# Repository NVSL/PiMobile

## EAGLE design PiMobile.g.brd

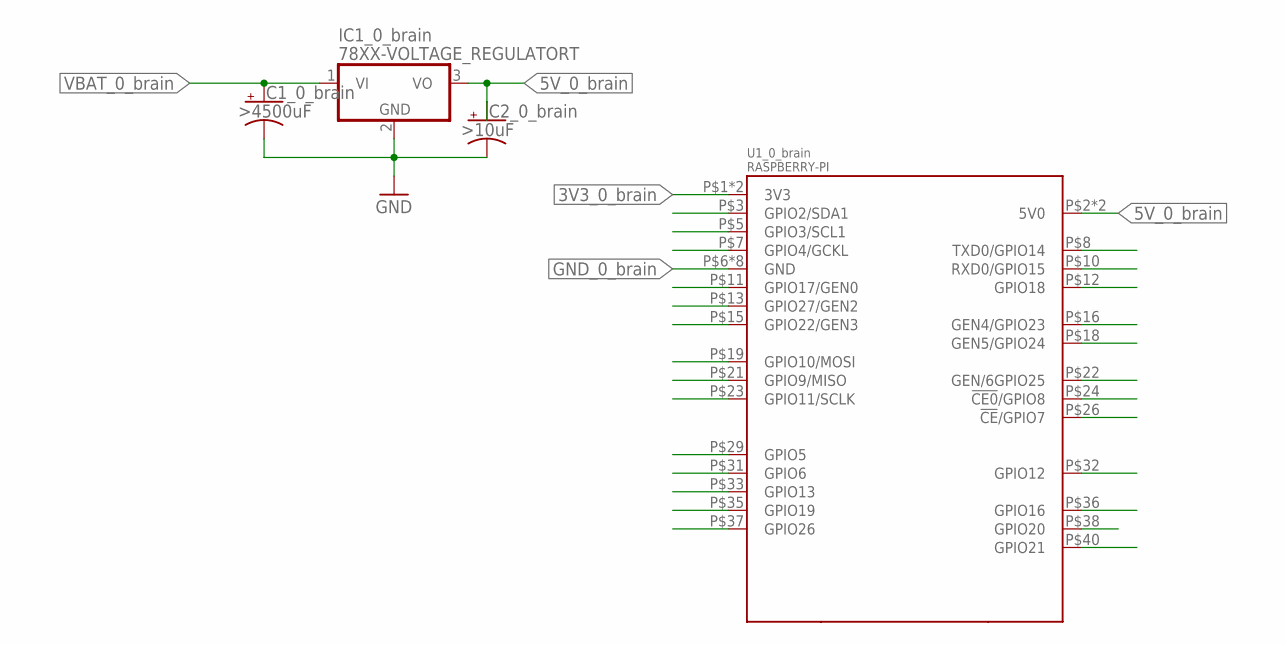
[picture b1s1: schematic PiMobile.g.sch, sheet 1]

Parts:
IC1_0_brain: 78XX-VOLTAGE_REGULATORT; TO220H
U1_0_brain: RASPBERRY-PI; RPI-ZERO-EDGE-RIGHT-ANGLE

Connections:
3V3_0_brain: U1_0_brain.P$1 (3V3), U1_0_brain.P$17 (3V3)
5V_0_brain: IC1_0_brain.3 (VO), U1_0_brain.P$2 (5V0), U1_0_brain.P$4 (5V0); also elsewhere on the board
!CE0!/GPIO8_0_brain: U1_0_brain.P$24 (!CE0!/GPIO8); also elsewhere on the board
!CE!/GPIO7_0_brain: U1_0_brain.P$26 (!CE!/GPIO7); also elsewhere on the board
GEN4/GPIO23_0_brain: U1_0_brain.P$16 (GEN4/GPIO23)
GEN5/GPIO24_0_brain: U1_0_brain.P$18 (GEN5/GPIO24)
GEN/6GPIO25_0_brain: U1_0_brain.P$22 (GEN/6GPIO25)
GND_0_brain: IC1_0_brain.2 (GND), U1_0_brain.P$6 (GND), U1_0_brain.P$9 (GND), U1_0_brain.P$14 (GND), U1_0_brain.P$20 (GND), U1_0_brain.P$25 (GND), U1_0_brain.P$30 (GND), U1_0_brain.P$34 (GND), U1_0_brain.P$39 (GND); also elsewhere on the board
GPIO2/SDA1_0_brain: U1_0_brain.P$3 (GPIO2/SDA1); also elsewhere on the board
GPIO3/SCL1_0_brain: U1_0_brain.P$5 (GPIO3/SCL1); also elsewhere on the board
GPIO4/GCKL_0_brain: U1_0_brain.P$7 (GPIO4/GCKL); also elsewhere on the board
GPIO5_0_brain: U1_0_brain.P$29 (GPIO5); also elsewhere on the board
GPIO6_0_brain: U1_0_brain.P$31 (GPIO6); also elsewhere on the board
GPIO9/MISO_0_brain: U1_0_brain.P$21 (GPIO9/MISO); also elsewhere on the board
GPIO10/MOSI_0_brain: U1_0_brain.P$19 (GPIO10/MOSI); also elsewhere on the board
GPIO11/SCLK_0_brain: U1_0_brain.P$23 (GPIO11/SCLK); also elsewhere on the board
GPIO12_0_brain: U1_0_brain.P$32 (GPIO12); also elsewhere on the board
GPIO13_0_brain: U1_0_brain.P$33 (GPIO13); also elsewhere on the board
GPIO16_0_brain: U1_0_brain.P$36 (GPIO16); also elsewhere on the board
GPIO17/GEN0_0_brain: U1_0_brain.P$11 (GPIO17/GEN0); also elsewhere on the board
GPIO18_0_brain: U1_0_brain.P$12 (GPIO18); also elsewhere on the board
GPIO19_0_brain: U1_0_brain.P$35 (GPIO19); also elsewhere on the board
GPIO20_0_brain: U1_0_brain.P$38 (GPIO20); also elsewhere on the board
GPIO21_0_brain: U1_0_brain.P$40 (GPIO21)
GPIO22/GEN3_0_brain: U1_0_brain.P$15 (GPIO22/GEN3)
GPIO26_0_brain: U1_0_brain.P$37 (GPIO26)
GPIO27/GEN2_0_brain: U1_0_brain.P$13 (GPIO27/GEN2)
RXD0/GPIO15_0_brain: U1_0_brain.P$10 (RXD0/GPIO15); also elsewhere on the board
TXD0/GPIO14_0_brain: U1_0_brain.P$8 (TXD0/GPIO14); also elsewhere on the board
VBAT_0_brain: IC1_0_brain.1 (VI)

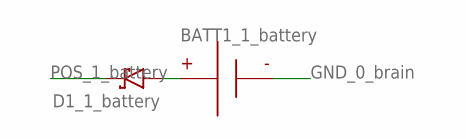
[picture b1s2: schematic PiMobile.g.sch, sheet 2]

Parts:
BATT1_1_battery: BATTERY-9V-VERTICAL; BATTERY_9V_KEYSTONE_968

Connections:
GND_0_brain: BATT1_1_battery.N; also elsewhere on the board

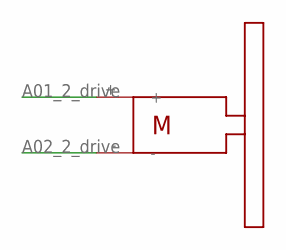
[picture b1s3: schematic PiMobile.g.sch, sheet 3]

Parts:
R_2_drive: SOLARBOTICS_GM2; SOLARBOTICS_G2

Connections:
A01_2_drive: R_2_drive.+; also elsewhere on the board
A02_2_drive: R_2_drive.-; also elsewhere on the board

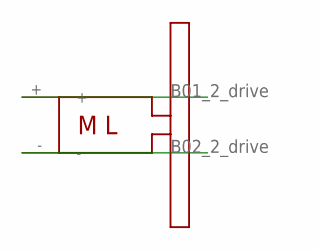
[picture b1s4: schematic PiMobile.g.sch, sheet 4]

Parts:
L_2_drive: SOLARBOTICS_GM2_LEFT; SOLARBOTICS_G2_LEFT

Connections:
B01_2_drive: L_2_drive.+; also elsewhere on the board
B02_2_drive: L_2_drive.-; also elsewhere on the board

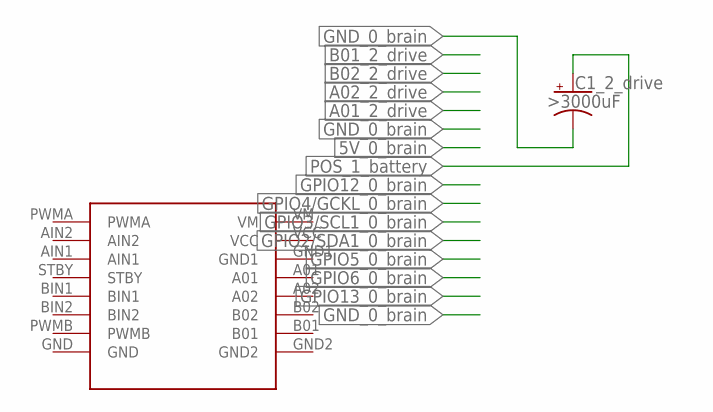
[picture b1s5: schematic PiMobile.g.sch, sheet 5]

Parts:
DRVR_2_drive: SPARKFUN_DUAL_MOTOR_DRIVER-BOB; SPARKFUN_DUAL_MOTOR_DRIVER

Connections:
5V_0_brain: DRVR_2_drive.VCC; also elsewhere on the board
A01_2_drive: DRVR_2_drive.A01; also elsewhere on the board
A02_2_drive: DRVR_2_drive.A02; also elsewhere on the board
B01_2_drive: DRVR_2_drive.B01; also elsewhere on the board
B02_2_drive: DRVR_2_drive.B02; also elsewhere on the board
GND_0_brain: DRVR_2_drive.GND, DRVR_2_drive.GND1, DRVR_2_drive.GND2; also elsewhere on the board
GPIO2/SDA1_0_brain: DRVR_2_drive.STBY; also elsewhere on the board
GPIO3/SCL1_0_brain: DRVR_2_drive.AIN1; also elsewhere on the board
GPIO4/GCKL_0_brain: DRVR_2_drive.AIN2; also elsewhere on the board
GPIO5_0_brain: DRVR_2_drive.BIN1; also elsewhere on the board
GPIO6_0_brain: DRVR_2_drive.BIN2; also elsewhere on the board
GPIO12_0_brain: DRVR_2_drive.PWMA; also elsewhere on the board
GPIO13_0_brain: DRVR_2_drive.PWMB; also elsewhere on the board
POS_1_battery: DRVR_2_drive.VM

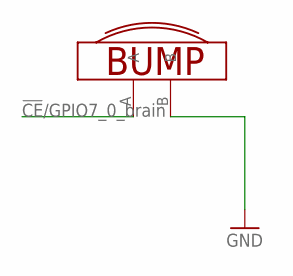
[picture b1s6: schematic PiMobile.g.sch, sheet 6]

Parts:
U$2_3_bump: BUMP_SWITCH-MEDIUM-LEFT; BUMP_SWITCH_OMRON_D2FLA

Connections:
!CE!/GPIO7_0_brain: U$2_3_bump.A; also elsewhere on the board
GND_0_brain: U$2_3_bump.B; also elsewhere on the board

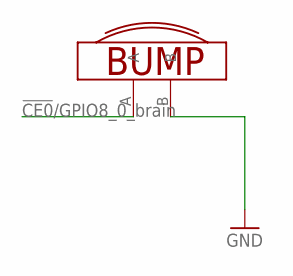
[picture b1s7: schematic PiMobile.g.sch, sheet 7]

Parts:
U$2_4_bump_2: BUMP_SWITCH-MEDIUM-RIGHT; BUMP_SWITCH_OMRON_D2FLA1

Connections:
!CE0!/GPIO8_0_brain: U$2_4_bump_2.A; also elsewhere on the board
GND_0_brain: U$2_4_bump_2.B; also elsewhere on the board

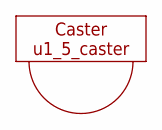
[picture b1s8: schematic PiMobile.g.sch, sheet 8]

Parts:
u1_5_caster: CASTERADAFRUIT-3/4IN; ADAFRUIT-3/4IN-CASTER

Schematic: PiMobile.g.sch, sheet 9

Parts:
LED1_6_led: LED5MM

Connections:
GPIO9/MISO_0_brain: LED1_6_led.A; also elsewhere on the board

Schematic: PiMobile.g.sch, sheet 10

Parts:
LED1_7_led_2: LED5MM

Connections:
GPIO10/MOSI_0_brain: LED1_7_led_2.A; also elsewhere on the board

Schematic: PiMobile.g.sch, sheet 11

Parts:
U$2_8_bump_3: BUMP_SWITCH-MEDIUM-LEFT; BUMP_SWITCH_OMRON_D2FLA

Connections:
GND_0_brain: U$2_8_bump_3.B; also elsewhere on the board
GPIO11/SCLK_0_brain: U$2_8_bump_3.A; also elsewhere on the board

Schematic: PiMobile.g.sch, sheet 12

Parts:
U$2_9_bump_4: BUMP_SWITCH-MEDIUM-RIGHT; BUMP_SWITCH_OMRON_D2FLA1

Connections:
GND_0_brain: U$2_9_bump_4.B; also elsewhere on the board
TXD0/GPIO14_0_brain: U$2_9_bump_4.A; also elsewhere on the board

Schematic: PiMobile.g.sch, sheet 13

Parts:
u1_10_penholder: PENHOLDER

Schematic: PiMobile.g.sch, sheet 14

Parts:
B1_11_button: BUTTON-TACTILE-ROUND; BUTTON-TACTILE-ROUND-ADAFRUIT1009

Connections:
GND_0_brain: B1_11_button.S; also elsewhere on the board
RXD0/GPIO15_0_brain: B1_11_button.P; also elsewhere on the board

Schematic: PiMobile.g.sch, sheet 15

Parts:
B1_12_button_2: BUTTON-TACTILE-ROUND; BUTTON-TACTILE-ROUND-ADAFRUIT1009

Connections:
GND_0_brain: B1_12_button_2.S; also elsewhere on the board
GPIO16_0_brain: B1_12_button_2.P; also elsewhere on the board

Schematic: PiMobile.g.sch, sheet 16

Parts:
LED1_13_led_3: LED5MM

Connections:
GPIO17/GEN0_0_brain: LED1_13_led_3.A; also elsewhere on the board

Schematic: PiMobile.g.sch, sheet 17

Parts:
LED1_14_led_4: LED5MM

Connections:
GPIO18_0_brain: LED1_14_led_4.A; also elsewhere on the board

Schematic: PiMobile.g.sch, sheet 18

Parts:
LED1_15_led_5: LED5MM

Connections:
GPIO19_0_brain: LED1_15_led_5.A; also elsewhere on the board

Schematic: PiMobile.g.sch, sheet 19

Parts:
LED1_16_led_6: LED5MM

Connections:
GPIO20_0_brain: LED1_16_led_6.A; also elsewhere on the board

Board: 2 copper layers, 20 parts (0 on the bottom side), 26 nets, no tracks yet.

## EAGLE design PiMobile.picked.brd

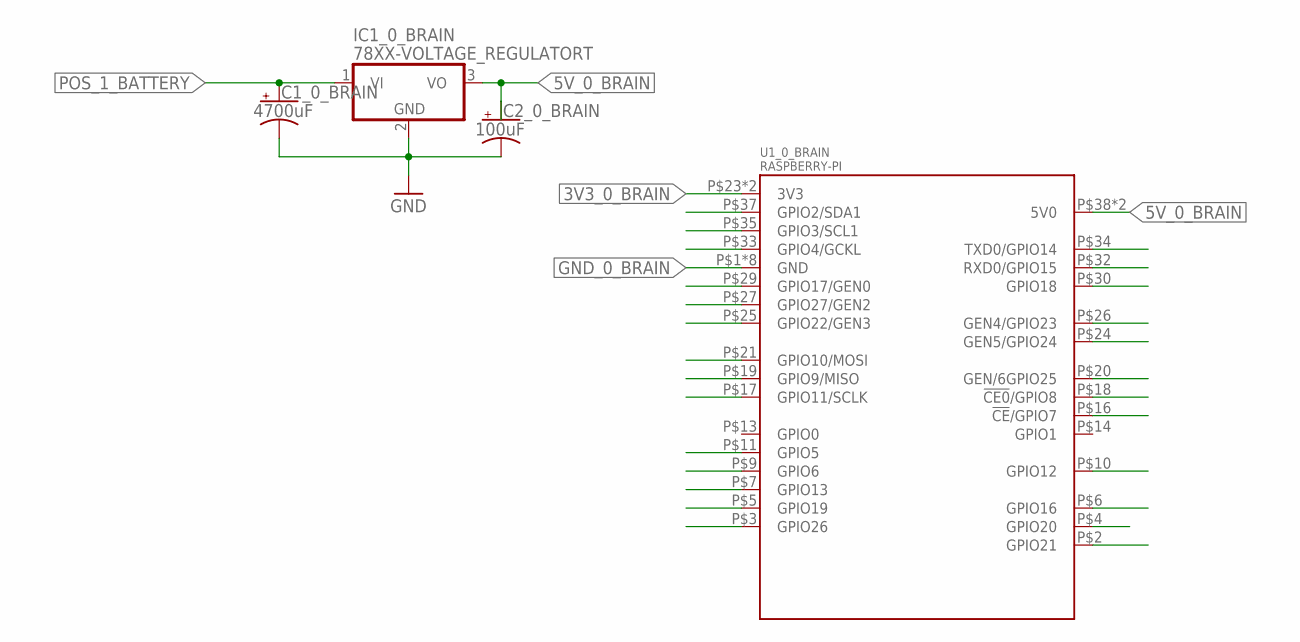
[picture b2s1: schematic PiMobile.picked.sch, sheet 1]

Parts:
C1_0_BRAIN: 4700uF; CAPPRD750W80D1600H2200P; MPN ECA-1EM472
C2_0_BRAIN: 100uF; CAPPRD250W80D630H1220P; MPN ECA-1EM101
IC1_0_BRAIN: 78XX-VOLTAGE_REGULATORT; TO220H
U1_0_BRAIN: RASPBERRY-PI; RPI-ZERO-EDGE-RIGHT-ANGLE

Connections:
3V3_0_BRAIN: U1_0_BRAIN.P$23 (3V3), U1_0_BRAIN.P$39 (3V3); also elsewhere on the board
5V_0_BRAIN: C2_0_BRAIN.1 (+), IC1_0_BRAIN.3 (VO), U1_0_BRAIN.P$38 (5V0), U1_0_BRAIN.P$40 (5V0)
!CE0!/GPIO8_0_BRAIN: U1_0_BRAIN.P$18 (!CE0!/GPIO8); also elsewhere on the board
!CE!/GPIO7_0_BRAIN: U1_0_BRAIN.P$16 (!CE!/GPIO7); also elsewhere on the board
GEN4/GPIO23_0_BRAIN: U1_0_BRAIN.P$26 (GEN4/GPIO23)
GEN5/GPIO24_0_BRAIN: U1_0_BRAIN.P$24 (GEN5/GPIO24)
GEN/6GPIO25_0_BRAIN: U1_0_BRAIN.P$20 (GEN/6GPIO25)
GND_0_BRAIN: C1_0_BRAIN.2 (-), C2_0_BRAIN.2 (-), IC1_0_BRAIN.2 (GND), U1_0_BRAIN.P$1 (GND), U1_0_BRAIN.P$8 (GND), U1_0_BRAIN.P$12 (GND), U1_0_BRAIN.P$15 (GND), U1_0_BRAIN.P$22 (GND), U1_0_BRAIN.P$28 (GND), U1_0_BRAIN.P$31 (GND), U1_0_BRAIN.P$36 (GND); also elsewhere on the board
GPIO2/SDA1_0_BRAIN: U1_0_BRAIN.P$37 (GPIO2/SDA1); also elsewhere on the board
GPIO3/SCL1_0_BRAIN: U1_0_BRAIN.P$35 (GPIO3/SCL1); also elsewhere on the board
GPIO4/GCKL_0_BRAIN: U1_0_BRAIN.P$33 (GPIO4/GCKL); also elsewhere on the board
GPIO5_0_BRAIN: U1_0_BRAIN.P$11 (GPIO5); also elsewhere on the board
GPIO6_0_BRAIN: U1_0_BRAIN.P$9 (GPIO6); also elsewhere on the board
GPIO9/MISO_0_BRAIN: U1_0_BRAIN.P$19 (GPIO9/MISO); also elsewhere on the board
GPIO10/MOSI_0_BRAIN: U1_0_BRAIN.P$21 (GPIO10/MOSI); also elsewhere on the board
GPIO11/SCLK_0_BRAIN: U1_0_BRAIN.P$17 (GPIO11/SCLK); also elsewhere on the board
GPIO12_0_BRAIN: U1_0_BRAIN.P$10 (GPIO12); also elsewhere on the board
GPIO13_0_BRAIN: U1_0_BRAIN.P$7 (GPIO13); also elsewhere on the board
GPIO16_0_BRAIN: U1_0_BRAIN.P$6 (GPIO16); also elsewhere on the board
GPIO17/GEN0_0_BRAIN: U1_0_BRAIN.P$29 (GPIO17/GEN0); also elsewhere on the board
GPIO18_0_BRAIN: U1_0_BRAIN.P$30 (GPIO18); also elsewhere on the board
GPIO19_0_BRAIN: U1_0_BRAIN.P$5 (GPIO19); also elsewhere on the board
GPIO20_0_BRAIN: U1_0_BRAIN.P$4 (GPIO20); also elsewhere on the board
GPIO21_0_BRAIN: U1_0_BRAIN.P$2 (GPIO21)
GPIO22/GEN3_0_BRAIN: U1_0_BRAIN.P$25 (GPIO22/GEN3)
GPIO26_0_BRAIN: U1_0_BRAIN.P$3 (GPIO26)
GPIO27/GEN2_0_BRAIN: U1_0_BRAIN.P$27 (GPIO27/GEN2)
POS_1_BATTERY: C1_0_BRAIN.1 (+), IC1_0_BRAIN.1 (VI); also elsewhere on the board
RXD0/GPIO15_0_BRAIN: U1_0_BRAIN.P$32 (RXD0/GPIO15); also elsewhere on the board
TXD0/GPIO14_0_BRAIN: U1_0_BRAIN.P$34 (TXD0/GPIO14); also elsewhere on the board

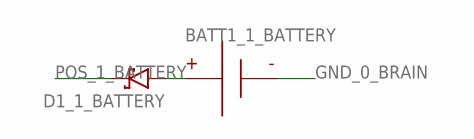
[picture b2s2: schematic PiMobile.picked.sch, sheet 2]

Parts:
BATT1_1_BATTERY: BATTERY-9V-VERTICAL; BATTERY_9V_KEYSTONE_968
D1_1_BATTERY: RESOLVED-DIODE-SCHOTTKY_TH-DO-41-AND-DO-204AL; DIOAD1125W78L520D270_HS; MPN 1N5817

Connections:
GND_0_BRAIN: BATT1_1_BATTERY.N; also elsewhere on the board
unnamed: BATT1_1_BATTERY.P, D1_1_BATTERY.A
POS_1_BATTERY: D1_1_BATTERY.C; also elsewhere on the board

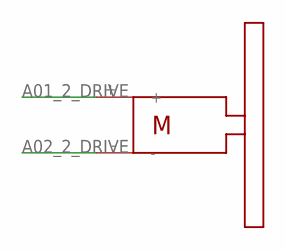
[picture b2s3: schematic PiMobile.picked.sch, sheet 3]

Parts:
R_2_DRIVE: SOLARBOTICS_GM2; SOLARBOTICS_G2

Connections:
A01_2_DRIVE: R_2_DRIVE.+; also elsewhere on the board
A02_2_DRIVE: R_2_DRIVE.-; also elsewhere on the board

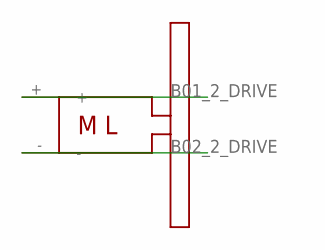
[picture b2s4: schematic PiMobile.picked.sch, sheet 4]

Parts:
L_2_DRIVE: SOLARBOTICS_GM2_LEFT; SOLARBOTICS_G2_LEFT

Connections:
B01_2_DRIVE: L_2_DRIVE.+; also elsewhere on the board
B02_2_DRIVE: L_2_DRIVE.-; also elsewhere on the board

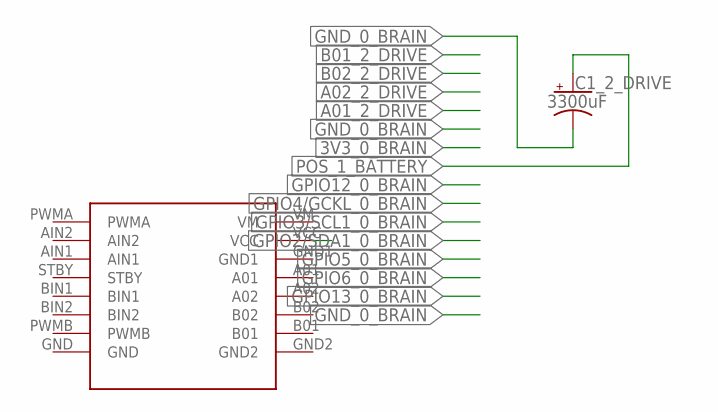
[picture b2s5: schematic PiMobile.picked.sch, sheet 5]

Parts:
C1_2_DRIVE: 3300uF; CAPPRD750W80D1600H2200P; MPN ECA-1EM332
DRVR_2_DRIVE: SPARKFUN_DUAL_MOTOR_DRIVER-BOB; SPARKFUN_DUAL_MOTOR_DRIVER

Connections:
3V3_0_BRAIN: DRVR_2_DRIVE.VCC; also elsewhere on the board
A01_2_DRIVE: DRVR_2_DRIVE.A01; also elsewhere on the board
A02_2_DRIVE: DRVR_2_DRIVE.A02; also elsewhere on the board
B01_2_DRIVE: DRVR_2_DRIVE.B01; also elsewhere on the board
B02_2_DRIVE: DRVR_2_DRIVE.B02; also elsewhere on the board
GND_0_BRAIN: C1_2_DRIVE.2 (-), DRVR_2_DRIVE.GND, DRVR_2_DRIVE.GND1, DRVR_2_DRIVE.GND2; also elsewhere on the board
GPIO2/SDA1_0_BRAIN: DRVR_2_DRIVE.STBY; also elsewhere on the board
GPIO3/SCL1_0_BRAIN: DRVR_2_DRIVE.AIN1; also elsewhere on the board
GPIO4/GCKL_0_BRAIN: DRVR_2_DRIVE.AIN2; also elsewhere on the board
GPIO5_0_BRAIN: DRVR_2_DRIVE.BIN1; also elsewhere on the board
GPIO6_0_BRAIN: DRVR_2_DRIVE.BIN2; also elsewhere on the board
GPIO12_0_BRAIN: DRVR_2_DRIVE.PWMA; also elsewhere on the board
GPIO13_0_BRAIN: DRVR_2_DRIVE.PWMB; also elsewhere on the board
POS_1_BATTERY: C1_2_DRIVE.1 (+), DRVR_2_DRIVE.VM; also elsewhere on the board

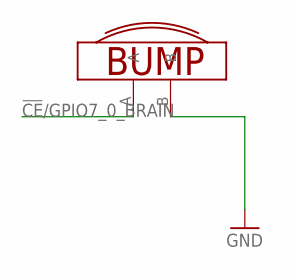
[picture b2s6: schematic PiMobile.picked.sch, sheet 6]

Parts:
U$2_3_BUMP: BUMP_SWITCH-MEDIUM-LEFT; BUMP_SWITCH_OMRON_D2FLA

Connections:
!CE!/GPIO7_0_BRAIN: U$2_3_BUMP.A; also elsewhere on the board
GND_0_BRAIN: U$2_3_BUMP.B; also elsewhere on the board

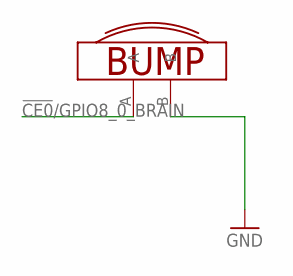
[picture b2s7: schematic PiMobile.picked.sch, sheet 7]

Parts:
U$2_4_BUMP_2: BUMP_SWITCH-MEDIUM-RIGHT; BUMP_SWITCH_OMRON_D2FLA1

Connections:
!CE0!/GPIO8_0_BRAIN: U$2_4_BUMP_2.A; also elsewhere on the board
GND_0_BRAIN: U$2_4_BUMP_2.B; also elsewhere on the board

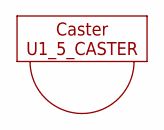
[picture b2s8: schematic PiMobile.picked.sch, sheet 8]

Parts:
U1_5_CASTER: CASTERADAFRUIT-3/4IN; ADAFRUIT-3/4IN-CASTER

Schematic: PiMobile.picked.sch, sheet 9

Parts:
LED1_6_LED: LED5MM
R1_6_LED: 330; RESAD770W45L370D210_HS; MPN CFR-12JB-52-330R

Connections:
GND_0_BRAIN: R1_6_LED.2; also elsewhere on the board
GPIO9/MISO_0_BRAIN: LED1_6_LED.A; also elsewhere on the board
unnamed: LED1_6_LED.K (C), R1_6_LED.1

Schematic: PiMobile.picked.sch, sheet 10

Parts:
LED1_7_LED_2: LED5MM
R1_7_LED_2: 330; RESAD770W45L370D210_HS; MPN CFR-12JB-52-330R

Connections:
GND_0_BRAIN: R1_7_LED_2.2; also elsewhere on the board
GPIO10/MOSI_0_BRAIN: LED1_7_LED_2.A; also elsewhere on the board
unnamed: LED1_7_LED_2.K (C), R1_7_LED_2.1

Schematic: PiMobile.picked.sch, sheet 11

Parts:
U$2_8_BUMP_3: BUMP_SWITCH-MEDIUM-LEFT; BUMP_SWITCH_OMRON_D2FLA

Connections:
GND_0_BRAIN: U$2_8_BUMP_3.B; also elsewhere on the board
GPIO11/SCLK_0_BRAIN: U$2_8_BUMP_3.A; also elsewhere on the board

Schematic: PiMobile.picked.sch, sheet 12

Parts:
U$2_9_BUMP_4: BUMP_SWITCH-MEDIUM-RIGHT; BUMP_SWITCH_OMRON_D2FLA1

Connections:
GND_0_BRAIN: U$2_9_BUMP_4.B; also elsewhere on the board
TXD0/GPIO14_0_BRAIN: U$2_9_BUMP_4.A; also elsewhere on the board

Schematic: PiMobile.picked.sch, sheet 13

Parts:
U1_10_PENHOLDER: PENHOLDER

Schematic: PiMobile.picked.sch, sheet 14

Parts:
B1_11_BUTTON: BUTTON-TACTILE-ROUND; BUTTON-TACTILE-ROUND-ADAFRUIT1009

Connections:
GND_0_BRAIN: B1_11_BUTTON.S; also elsewhere on the board
RXD0/GPIO15_0_BRAIN: B1_11_BUTTON.P; also elsewhere on the board

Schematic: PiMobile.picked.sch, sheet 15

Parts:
B1_12_BUTTON_2: BUTTON-TACTILE-ROUND; BUTTON-TACTILE-ROUND-ADAFRUIT1009

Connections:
GND_0_BRAIN: B1_12_BUTTON_2.S; also elsewhere on the board
GPIO16_0_BRAIN: B1_12_BUTTON_2.P; also elsewhere on the board

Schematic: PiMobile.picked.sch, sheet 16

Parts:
LED1_13_LED_3: LED5MM
R1_13_LED_3: 330; RESAD770W45L370D210_HS; MPN CFR-12JB-52-330R

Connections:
GND_0_BRAIN: R1_13_LED_3.2; also elsewhere on the board
GPIO17/GEN0_0_BRAIN: LED1_13_LED_3.A; also elsewhere on the board
unnamed: LED1_13_LED_3.K (C), R1_13_LED_3.1

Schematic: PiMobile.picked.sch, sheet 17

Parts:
LED1_14_LED_4: LED5MM
R1_14_LED_4: 330; RESAD770W45L370D210_HS; MPN CFR-12JB-52-330R

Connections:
GND_0_BRAIN: R1_14_LED_4.2; also elsewhere on the board
GPIO18_0_BRAIN: LED1_14_LED_4.A; also elsewhere on the board
unnamed: LED1_14_LED_4.K (C), R1_14_LED_4.1

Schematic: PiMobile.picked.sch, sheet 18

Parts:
LED1_15_LED_5: LED5MM
R1_15_LED_5: 330; RESAD770W45L370D210_HS; MPN CFR-12JB-52-330R

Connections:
GND_0_BRAIN: R1_15_LED_5.2; also elsewhere on the board
GPIO19_0_BRAIN: LED1_15_LED_5.A; also elsewhere on the board
unnamed: LED1_15_LED_5.K (C), R1_15_LED_5.1

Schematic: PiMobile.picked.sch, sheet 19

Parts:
LED1_16_LED_6: LED5MM
R1_16_LED_6: 330; RESAD770W45L370D210_HS; MPN CFR-12JB-52-330R

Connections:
GND_0_BRAIN: R1_16_LED_6.2; also elsewhere on the board
GPIO20_0_BRAIN: LED1_16_LED_6.A; also elsewhere on the board
unnamed: LED1_16_LED_6.K (C), R1_16_LED_6.1

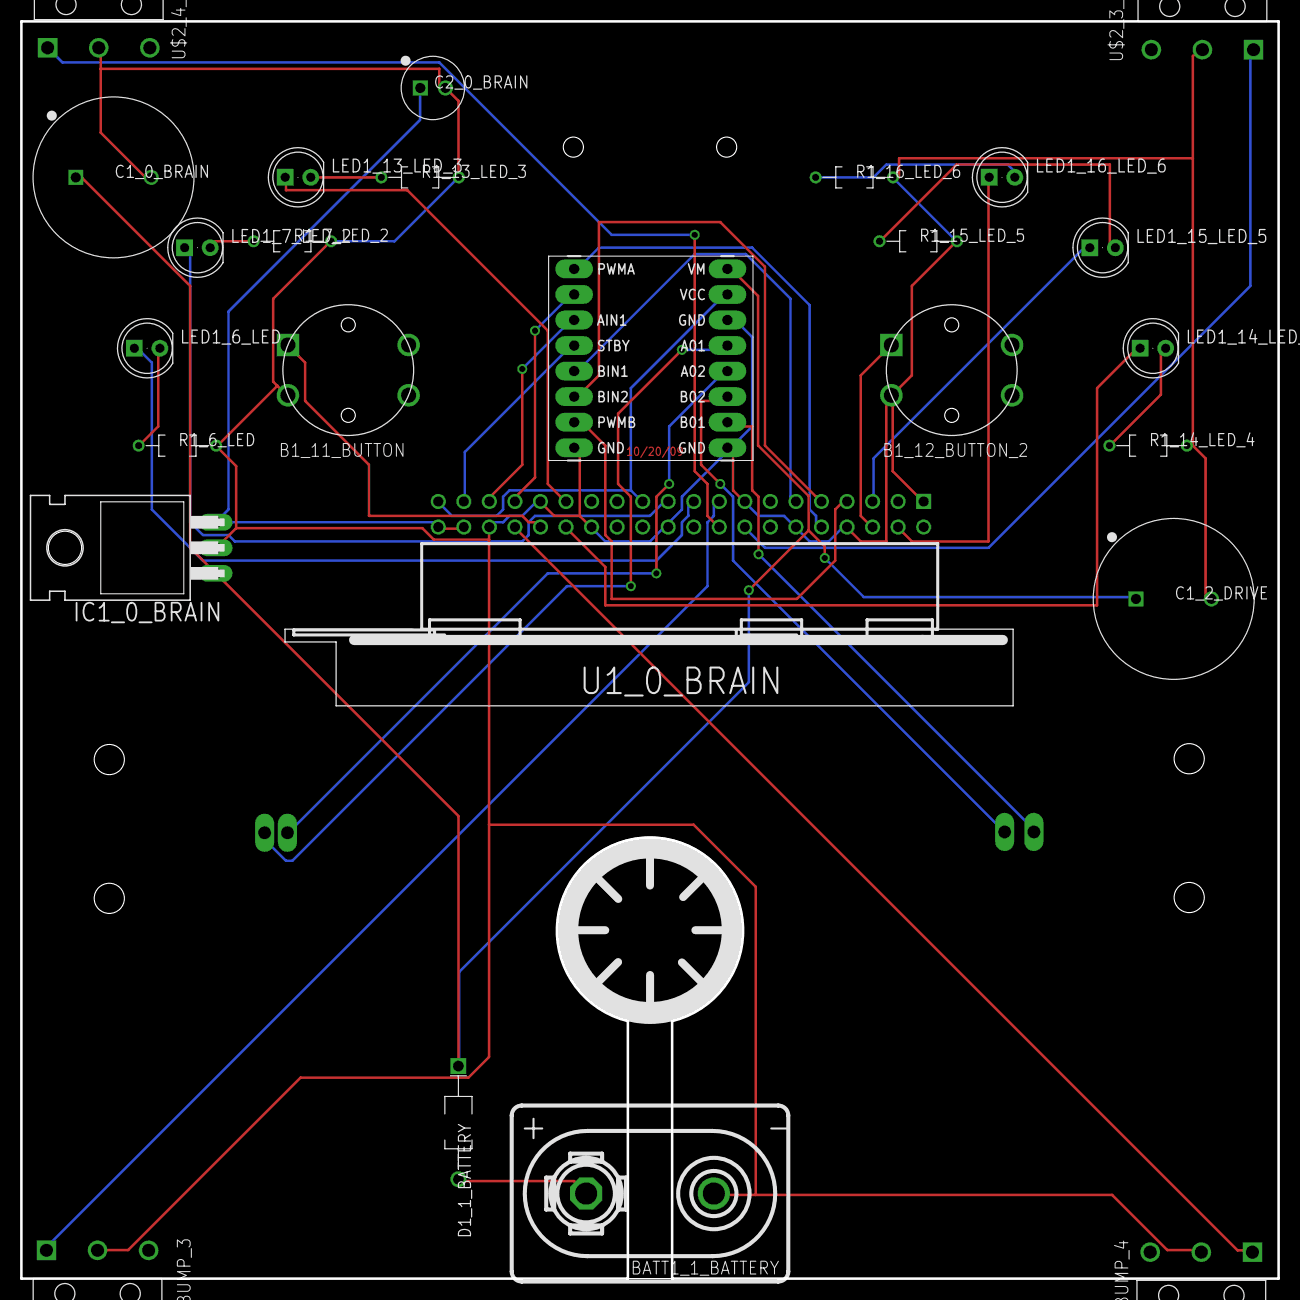
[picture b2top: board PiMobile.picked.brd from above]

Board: 2 copper layers, 125.0 x 125.0 mm, 30 parts (0 on the bottom side), 34 nets.

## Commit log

2016-03-30 got rid of cut out. Ordered boards
